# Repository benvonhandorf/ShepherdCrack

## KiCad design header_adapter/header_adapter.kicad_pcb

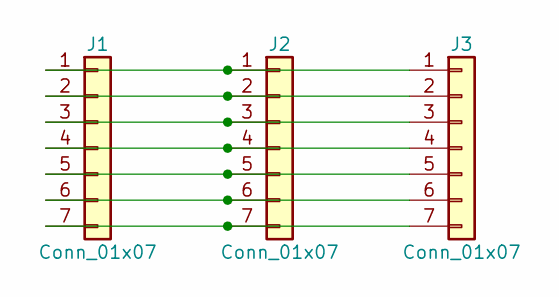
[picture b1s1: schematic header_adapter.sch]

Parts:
J1, J2: Conn_01x07; Pin_Header_Straight_1x07_Pitch1.27mm
J3: Conn_01x07; Pin_Header_Straight_1x07_Pitch2.54mm

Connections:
unnamed: J1.1, J2.1, J3.1
unnamed: J1.2, J2.2, J3.2
unnamed: J1.3, J2.3, J3.3
unnamed: J1.4, J2.4, J3.4
unnamed: J1.5, J2.5, J3.5
unnamed: J1.6, J2.6, J3.6
unnamed: J1.7, J2.7, J3.7

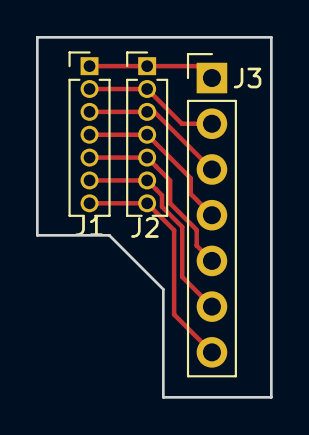
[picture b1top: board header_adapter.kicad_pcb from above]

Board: 2 copper layers, 13.0 x 20.0 mm, 3 parts (0 on the bottom side), 7 nets.

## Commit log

2017-10-20 Initial traces and analysis
2017-10-29 New traces with cs
2017-10-29 Getting closer to a sigrok protocol analyzer
2017-10-29 Protocol analyzer compiles, doesn't work yet
2017-10-29 Progress
2017-10-30 Work on protocol decoder
2017-10-31 TX Byte Stream working
2017-12-11 0.05in adapter PCB
2017-12-27 RX decoding in protocol analyzer, full RX capture set (minus tree ornament), first start on a TX test
2017-12-27 Before trying strict mimic mode
2018-02-14 Trailing commit
2022-07-02 Backup
